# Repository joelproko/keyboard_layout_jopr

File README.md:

# keyboard_layout_jopr
This is my first attempt at a custom keyboard. It's inspired, among others, by https://github.com/itractus/KeyBored  
The firmware is located at https://github.com/joelproko/qmk_firmware/tree/jopr

This is a layout of what the microcontroller will probably send for which key:  

"default":  
  
[Keyboard Layout Editor link](http://www.keyboard-layout-editor.com/#/gists/82594aeadc8321c39f5dd5e3733b16e5)

"modded-white": (based on https://github.com/mw8/white_keyboard_layout)  
  
[Keyboard Layout Editor link](http://www.keyboard-layout-editor.com/#/gists/e355f587c1d4540c1ec2808fc14671c6)

This a keycap design for the latter:  
  
[Keyboard Layout Editor link](http://www.keyboard-layout-editor.com/#/gists/73444aee1e5caa922be72c5b2b2db0ba)

There's a PDF of the schematic

and a PDF of the PCB
 (and [a version with separate pages for each layer](https://github.com/joelproko/keyboard_layout_jopr/raw/master/keyboard_layout_jopr.kicad_pcb.page_per_layer.pdf))

2019-06-22:  
So far, the PCB and the keycaps have arrived. I made a low quality photo on my phone.

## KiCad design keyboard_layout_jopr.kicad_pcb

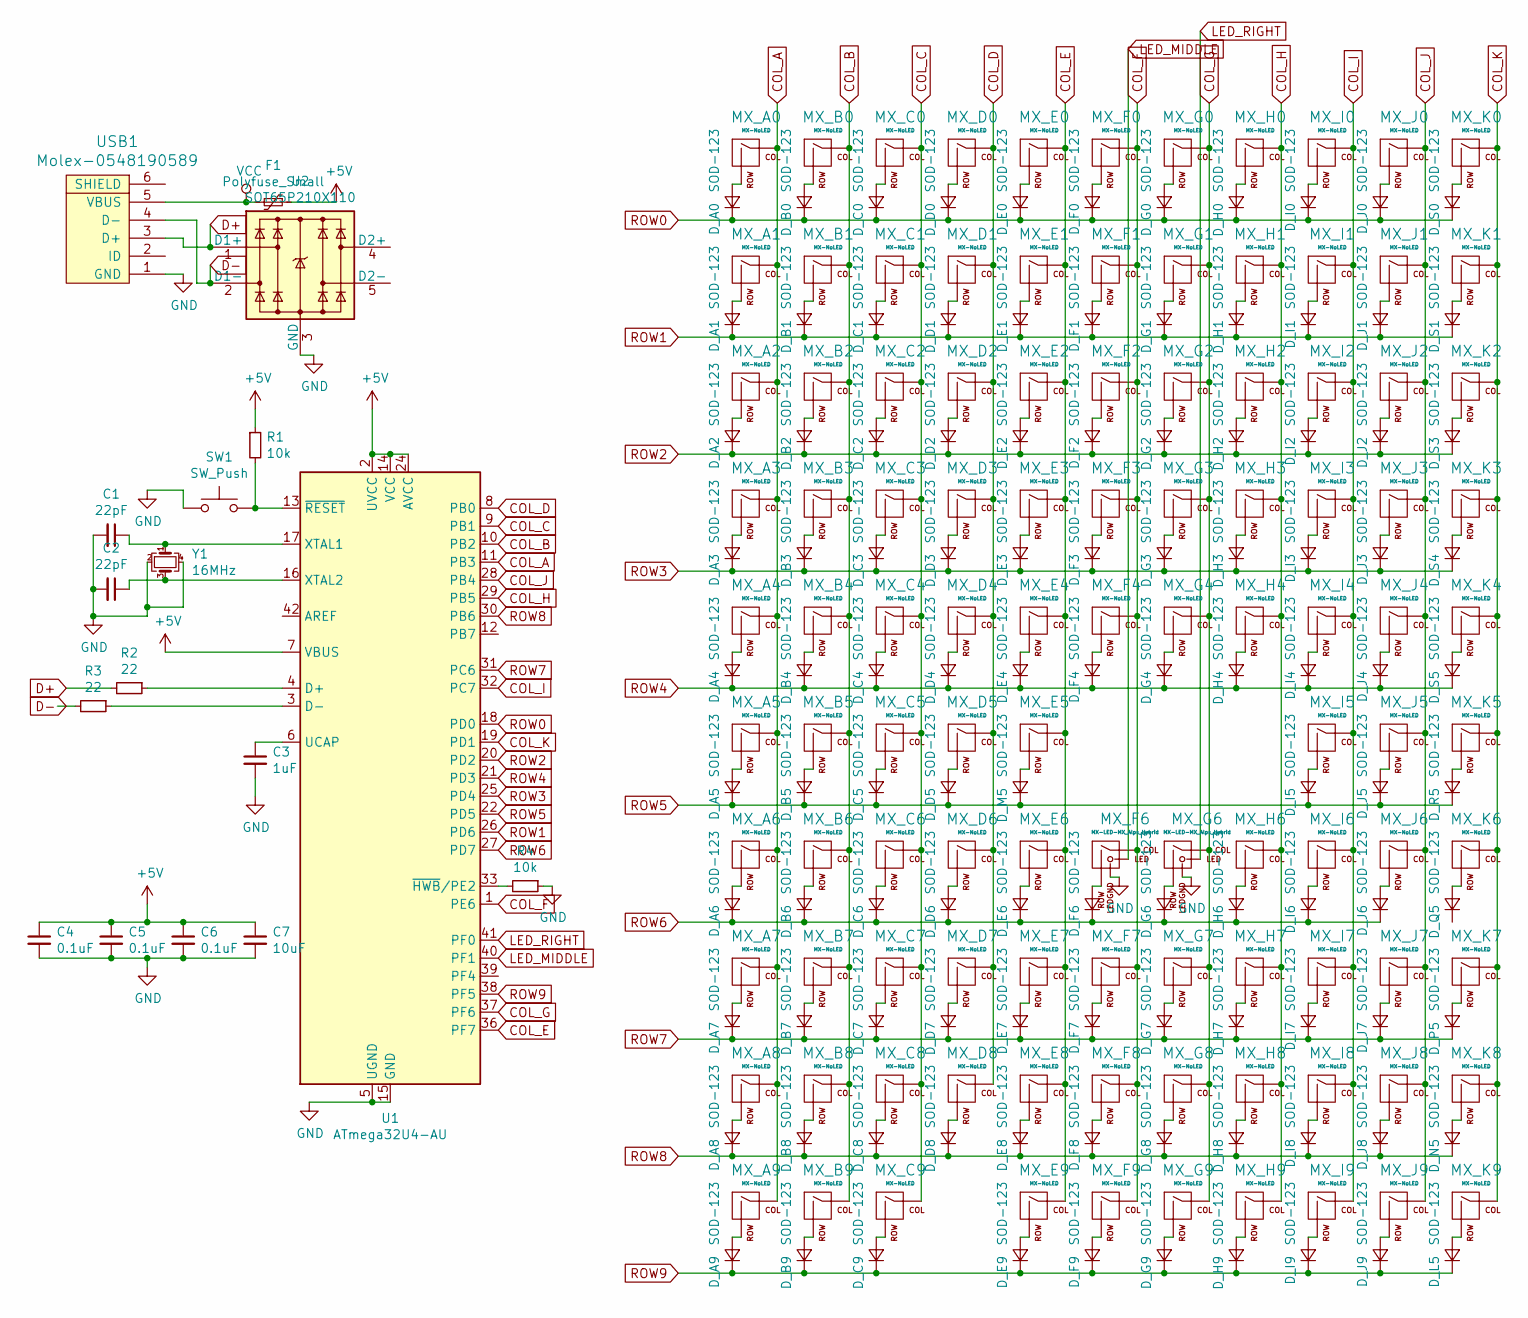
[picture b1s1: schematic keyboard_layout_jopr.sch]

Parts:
C1, C2: 22pF; C_0805_2012Metric
C3: 1uF; C_0805_2012Metric
C4, C5, C6: 0.1uF; C_0805_2012Metric
C7: 10uF; C_0805_2012Metric
D_A0, D_A1, D_A2, D_A3, D_A4, D_A5, D_A6, D_A7, D_A8, D_A9: SOD-123; D_SOD-123
D_B0, D_B1, D_B2, D_B3, D_B4, D_B5, D_B6, D_B7, D_B8, D_B9: SOD-123; D_SOD-123
D_C0, D_C1, D_C2, D_C3, D_C4, D_C5, D_C6, D_C7, D_C8, D_C9: SOD-123; D_SOD-123
D_D0, D_D1, D_D2, D_D3, D_D4, D_D5, D_D6, D_D7, D_D8: SOD-123; D_SOD-123
D_E0, D_E1, D_E2, D_E3, D_E4, D_E6, D_E7, D_E8, D_E9: SOD-123; D_SOD-123
D_F0, D_F1, D_F2, D_F3, D_F4, D_F6, D_F7, D_F8, D_F9: SOD-123; D_SOD-123
D_G0, D_G1, D_G2, D_G3, D_G4, D_G6, D_G7, D_G8, D_G9: SOD-123; D_SOD-123
D_H0, D_H1, D_H2, D_H3, D_H4, D_H6, D_H7, D_H8, D_H9: SOD-123; D_SOD-123
D_I0, D_I1, D_I2, D_I3, D_I4, D_I5, D_I6, D_I7, D_I8, D_I9: SOD-123; D_SOD-123
D_J0, D_J1, D_J2, D_J3, D_J4, D_J5, D_J6, D_J7, D_J8, D_J9: SOD-123; D_SOD-123
D_L5: SOD-123; D_SOD-123
D_M5: SOD-123; D_SOD-123
D_N5: SOD-123; D_SOD-123
D_P5: SOD-123; D_SOD-123
D_Q5: SOD-123; D_SOD-123
D_R5: SOD-123; D_SOD-123
D_S0, D_S1, D_S3, D_S4, D_S5: SOD-123; D_SOD-123
F1: Polyfuse_Small; Fuse_1206_3216Metric
MX_A0, MX_A1, MX_A6, MX_A7, MX_A8, MX_A9: MX-NoLED; MXOnly-1U-NoLED
MX_A2: MX-NoLED; MXOnly-1.5U-NoLED
MX_A3: MX-NoLED; MXOnly-1.75U-NoLED
MX_A4, MX_A5: MX-NoLED; MXOnly-1.25U-NoLED
MX_B0, MX_B1, MX_B2, MX_B3, MX_B4, MX_B6, MX_B7, MX_B8, MX_B9: MX-NoLED; MXOnly-1U-NoLED
MX_B5: MX-NoLED; MXOnly-1.25U-NoLED
MX_C0, MX_C1, MX_C2, MX_C3, MX_C4, MX_C6, MX_C7, MX_C8, MX_C9: MX-NoLED; MXOnly-1U-NoLED
MX_C5: MX-NoLED; MXOnly-1.25U-NoLED
MX_D0, MX_D1, MX_D2, MX_D3, MX_D4, MX_D6: MX-NoLED; MXOnly-1U-NoLED
MX_D5: MX-NoLED; MXOnly-6.25U-NoLED
MX_D7: MX-NoLED; MXOnly-2U-NoLED
MX_D8: MX-NoLED; MXOnly-ISO-NoLED
MX_E0, MX_E1, MX_E2, MX_E3, MX_E4, MX_E6, MX_E7, MX_E8, MX_E9: MX-NoLED; MXOnly-1U-NoLED
MX_E5: MX-NoLED; MXOnly-1.25U-NoLED
MX_F0, MX_F1, MX_F2, MX_F3, MX_F4, MX_F7, MX_F8, MX_F9: MX-NoLED; MXOnly-1U-NoLED
MX_F6: MX-LED-MX_Alps_Hybrid; MXOnly-1U-FLIPPED
MX_G0, MX_G1, MX_G2, MX_G3, MX_G4, MX_G7, MX_G8, MX_G9: MX-NoLED; MXOnly-1U-NoLED
MX_G6: MX-LED-MX_Alps_Hybrid; MXOnly-1U-FLIPPED
MX_H0, MX_H1, MX_H2, MX_H3, MX_H4, MX_H6, MX_H7, MX_H9: MX-NoLED; MXOnly-1U-NoLED
MX_H8: MX-NoLED; MXOnly-2U-NoLED
MX_I0, MX_I1, MX_I2, MX_I3, MX_I4, MX_I6, MX_I8, MX_I9: MX-NoLED; MXOnly-1U-NoLED
MX_I5: MX-NoLED; MXOnly-1.25U-NoLED
MX_I7: MX-NoLED; MXOnly-2.75U-NoLED
MX_J0, MX_J1, MX_J2, MX_J3, MX_J4, MX_J6, MX_J8, MX_J9: MX-NoLED; MXOnly-1U-NoLED
MX_J5: MX-NoLED; MXOnly-1.25U-NoLED
MX_J7: MX-NoLED; MXOnly-2U-NoLED
MX_K0, MX_K1, MX_K2, MX_K3, MX_K4, MX_K5, MX_K6, MX_K7: MX-NoLED; MXOnly-1U-NoLED
MX_K8: MX-NoLED; MXOnly-2U-NoLED
MX_K9: MX-NoLED; MXOnly-1.25U-NoLED
R1, R4: 10k; R_0805_2012Metric
R2, R3: 22; R_0805_2012Metric
SW1: SW_Push; SKQG-1155865
U1: ATmega32U4-AU; TQFP-44_10x10mm_P0.8mm
U2: SOT65P210X110; SOT65P210X110-6N
USB1: Molex-0548190589
Y1: 16MHz; Crystal_SMD_3225-4Pin_3.2x2.5mm

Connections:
+5V: C4.1, C5.1, C6.1, C7.1, F1.1, R1.1, U1.2 (UVCC), U1.7 (VBUS), U1.14 (VCC), U1.24 (AVCC), U1.34 (VCC), U1.44 (AVCC)
COL_A: MX_A0.1 (COL), MX_A1.1 (COL), MX_A2.1 (COL), MX_A3.1 (COL), MX_A4.1 (COL), MX_A5.1 (COL), MX_A6.1 (COL), MX_A7.1 (COL), MX_A8.1 (COL), MX_A9.1 (COL), U1.11 (PB3)
COL_B: MX_B0.1 (COL), MX_B1.1 (COL), MX_B2.1 (COL), MX_B3.1 (COL), MX_B4.1 (COL), MX_B5.1 (COL), MX_B6.1 (COL), MX_B7.1 (COL), MX_B8.1 (COL), MX_B9.1 (COL), U1.10 (PB2)
COL_C: MX_C0.1 (COL), MX_C1.1 (COL), MX_C2.1 (COL), MX_C3.1 (COL), MX_C4.1 (COL), MX_C5.1 (COL), MX_C6.1 (COL), MX_C7.1 (COL), MX_C8.1 (COL), MX_C9.1 (COL), U1.9 (PB1)
COL_D: MX_D0.1 (COL), MX_D1.1 (COL), MX_D2.1 (COL), MX_D3.1 (COL), MX_D4.1 (COL), MX_D5.1 (COL), MX_D6.1 (COL), MX_D7.1 (COL), MX_D8.1 (COL), U1.8 (PB0)
COL_E: MX_E0.1 (COL), MX_E1.1 (COL), MX_E2.1 (COL), MX_E3.1 (COL), MX_E4.1 (COL), MX_E5.1 (COL), MX_E6.1 (COL), MX_E7.1 (COL), MX_E8.1 (COL), MX_E9.1 (COL), U1.36 (PF7)
COL_F: MX_F0.1 (COL), MX_F1.1 (COL), MX_F2.1 (COL), MX_F3.1 (COL), MX_F4.1 (COL), MX_F6.1 (COL), MX_F7.1 (COL), MX_F8.1 (COL), MX_F9.1 (COL), U1.1 (PE6)
COL_G: MX_G0.1 (COL), MX_G1.1 (COL), MX_G2.1 (COL), MX_G3.1 (COL), MX_G4.1 (COL), MX_G6.1 (COL), MX_G7.1 (COL), MX_G8.1 (COL), MX_G9.1 (COL), U1.37 (PF6)
COL_H: MX_H0.1 (COL), MX_H1.1 (COL), MX_H2.1 (COL), MX_H3.1 (COL), MX_H4.1 (COL), MX_H6.1 (COL), MX_H7.1 (COL), MX_H8.1 (COL), MX_H9.1 (COL), U1.29 (PB5)
COL_I: MX_I0.1 (COL), MX_I1.1 (COL), MX_I2.1 (COL), MX_I3.1 (COL), MX_I4.1 (COL), MX_I5.1 (COL), MX_I6.1 (COL), MX_I7.1 (COL), MX_I8.1 (COL), MX_I9.1 (COL), U1.32 (PC7)
COL_J: MX_J0.1 (COL), MX_J1.1 (COL), MX_J2.1 (COL), MX_J3.1 (COL), MX_J4.1 (COL), MX_J5.1 (COL), MX_J6.1 (COL), MX_J7.1 (COL), MX_J8.1 (COL), MX_J9.1 (COL), U1.28 (PB4)
COL_K: MX_K0.1 (COL), MX_K1.1 (COL), MX_K2.1 (COL), MX_K3.1 (COL), MX_K4.1 (COL), MX_K5.1 (COL), MX_K6.1 (COL), MX_K7.1 (COL), MX_K8.1 (COL), MX_K9.1 (COL), U1.19 (PD1)
D+: R2.2, U2.1 (D1+), USB1.3 (D+)
D-: R3.2, U2.2 (D1-), USB1.4 (D-)
GND: C1.2, C2.2, C3.2, C4.2, C5.2, C6.2, C7.2, MX_F6.4 (LEDGND), MX_G6.4 (LEDGND), R4.1, SW1.1, U1.5 (UGND), U1.15 (GND), U1.23 (GND), U1.35 (GND), U1.43 (GND), U2.3 (GND), U2.8 (GND), USB1.1 (GND), Y1.2, Y1.4
LED_MIDDLE: MX_F6.3 (LED), U1.40 (PF1)
LED_RIGHT: MX_G6.3 (LED), U1.41 (PF0)
unnamed: C1.1, U1.17 (XTAL1), Y1.1
unnamed: C2.1, U1.16 (XTAL2), Y1.3
unnamed: C3.1, U1.6 (UCAP)
unnamed: D_A0.2 (A), MX_A0.2 (ROW)
unnamed: D_A1.2 (A), MX_A1.2 (ROW)
unnamed: D_A2.2 (A), MX_A2.2 (ROW)
unnamed: D_A3.2 (A), MX_A3.2 (ROW)
unnamed: D_A4.2 (A), MX_A4.2 (ROW)
unnamed: D_A5.2 (A), MX_A5.2 (ROW)
unnamed: D_A6.2 (A), MX_A6.2 (ROW)
unnamed: D_A7.2 (A), MX_A7.2 (ROW)
unnamed: D_A8.2 (A), MX_A8.2 (ROW)
unnamed: D_A9.2 (A), MX_A9.2 (ROW)
unnamed: D_B0.2 (A), MX_B0.2 (ROW)
unnamed: D_B1.2 (A), MX_B1.2 (ROW)
unnamed: D_B2.2 (A), MX_B2.2 (ROW)
unnamed: D_B3.2 (A), MX_B3.2 (ROW)
unnamed: D_B4.2 (A), MX_B4.2 (ROW)
unnamed: D_B5.2 (A), MX_B5.2 (ROW)
unnamed: D_B6.2 (A), MX_B6.2 (ROW)
unnamed: D_B7.2 (A), MX_B7.2 (ROW)
unnamed: D_B8.2 (A), MX_B8.2 (ROW)
unnamed: D_B9.2 (A), MX_B9.2 (ROW)
unnamed: D_C0.2 (A), MX_C0.2 (ROW)
unnamed: D_C1.2 (A), MX_C1.2 (ROW)
unnamed: D_C2.2 (A), MX_C2.2 (ROW)
unnamed: D_C3.2 (A), MX_C3.2 (ROW)
unnamed: D_C4.2 (A), MX_C4.2 (ROW)
unnamed: D_C5.2 (A), MX_C5.2 (ROW)
unnamed: D_C6.2 (A), MX_C6.2 (ROW)
unnamed: D_C7.2 (A), MX_C7.2 (ROW)
unnamed: D_C8.2 (A), MX_C8.2 (ROW)
unnamed: D_C9.2 (A), MX_C9.2 (ROW)
unnamed: D_D0.2 (A), MX_D0.2 (ROW)
unnamed: D_D1.2 (A), MX_D1.2 (ROW)
unnamed: D_D2.2 (A), MX_D2.2 (ROW)
unnamed: D_D3.2 (A), MX_D3.2 (ROW)
unnamed: D_D4.2 (A), MX_D4.2 (ROW)
unnamed: D_D5.2 (A), MX_D5.2 (ROW)
unnamed: D_D6.2 (A), MX_D6.2 (ROW)
unnamed: D_D7.2 (A), MX_D7.2 (ROW)
unnamed: D_D8.2 (A), MX_D8.2 (ROW)
unnamed: D_E0.2 (A), MX_E0.2 (ROW)
unnamed: D_E1.2 (A), MX_E1.2 (ROW)
unnamed: D_E2.2 (A), MX_E2.2 (ROW)
unnamed: D_E3.2 (A), MX_E3.2 (ROW)
unnamed: D_E4.2 (A), MX_E4.2 (ROW)
unnamed: D_E6.2 (A), MX_E6.2 (ROW)
unnamed: D_E7.2 (A), MX_E7.2 (ROW)
unnamed: D_E8.2 (A), MX_E8.2 (ROW)
unnamed: D_E9.2 (A), MX_E9.2 (ROW)
unnamed: D_F0.2 (A), MX_F0.2 (ROW)
unnamed: D_F1.2 (A), MX_F1.2 (ROW)
unnamed: D_F2.2 (A), MX_F2.2 (ROW)
unnamed: D_F3.2 (A), MX_F3.2 (ROW)
unnamed: D_F4.2 (A), MX_F4.2 (ROW)
unnamed: D_F6.2 (A), MX_F6.2 (ROW)
unnamed: D_F7.2 (A), MX_F7.2 (ROW)
unnamed: D_F8.2 (A), MX_F8.2 (ROW)
unnamed: D_F9.2 (A), MX_F9.2 (ROW)
unnamed: D_G0.2 (A), MX_G0.2 (ROW)
unnamed: D_G1.2 (A), MX_G1.2 (ROW)
unnamed: D_G2.2 (A), MX_G2.2 (ROW)
unnamed: D_G3.2 (A), MX_G3.2 (ROW)
unnamed: D_G4.2 (A), MX_G4.2 (ROW)
unnamed: D_G6.2 (A), MX_G6.2 (ROW)
unnamed: D_G7.2 (A), MX_G7.2 (ROW)
unnamed: D_G8.2 (A), MX_G8.2 (ROW)
unnamed: D_G9.2 (A), MX_G9.2 (ROW)
unnamed: D_H0.2 (A), MX_H0.2 (ROW)
unnamed: D_H1.2 (A), MX_H1.2 (ROW)
unnamed: D_H2.2 (A), MX_H2.2 (ROW)
unnamed: D_H3.2 (A), MX_H3.2 (ROW)
unnamed: D_H4.2 (A), MX_H4.2 (ROW)
unnamed: D_H6.2 (A), MX_H6.2 (ROW)
unnamed: D_H7.2 (A), MX_H7.2 (ROW)
unnamed: D_H8.2 (A), MX_H8.2 (ROW)
unnamed: D_H9.2 (A), MX_H9.2 (ROW)
unnamed: D_I0.2 (A), MX_I0.2 (ROW)
unnamed: D_I1.2 (A), MX_I1.2 (ROW)
unnamed: D_I2.2 (A), MX_I2.2 (ROW)
unnamed: D_I3.2 (A), MX_I3.2 (ROW)
unnamed: D_I4.2 (A), MX_I4.2 (ROW)
unnamed: D_I5.2 (A), MX_I5.2 (ROW)
unnamed: D_I6.2 (A), MX_I6.2 (ROW)
unnamed: D_I7.2 (A), MX_I7.2 (ROW)
unnamed: D_I8.2 (A), MX_I8.2 (ROW)
unnamed: D_I9.2 (A), MX_I9.2 (ROW)
unnamed: D_J0.2 (A), MX_J0.2 (ROW)
unnamed: D_J1.2 (A), MX_J1.2 (ROW)
unnamed: D_J2.2 (A), MX_J2.2 (ROW)
unnamed: D_J3.2 (A), MX_J3.2 (ROW)
unnamed: D_J4.2 (A), MX_J4.2 (ROW)
unnamed: D_J5.2 (A), MX_J5.2 (ROW)
unnamed: D_J6.2 (A), MX_J6.2 (ROW)
unnamed: D_J7.2 (A), MX_J7.2 (ROW)
unnamed: D_J8.2 (A), MX_J8.2 (ROW)
unnamed: D_J9.2 (A), MX_J9.2 (ROW)
unnamed: D_L5.2 (A), MX_K9.2 (ROW)
unnamed: D_M5.2 (A), MX_E5.2 (ROW)
unnamed: D_N5.2 (A), MX_K8.2 (ROW)
unnamed: D_P5.2 (A), MX_K7.2 (ROW)
unnamed: D_Q5.2 (A), MX_K6.2 (ROW)
unnamed: D_R5.2 (A), MX_K5.2 (ROW)
unnamed: D_S0.2 (A), MX_K0.2 (ROW)
unnamed: D_S1.2 (A), MX_K1.2 (ROW)
unnamed: D_S3.2 (A), MX_K2.2 (ROW)
unnamed: D_S4.2 (A), MX_K3.2 (ROW)
unnamed: D_S5.2 (A), MX_K4.2 (ROW)
unnamed: R1.2, SW1.2, U1.13 (~RESET)
unnamed: R2.1, U1.4 (D+)
unnamed: R3.1, U1.3 (D-)
unnamed: R4.2, U1.33 (~HWB~/PE2)
ROW0: D_A0.1 (K), D_B0.1 (K), D_C0.1 (K), D_D0.1 (K), D_E0.1 (K), D_F0.1 (K), D_G0.1 (K), D_H0.1 (K), D_I0.1 (K), D_J0.1 (K), D_S0.1 (K), U1.18 (PD0)
ROW1: D_A1.1 (K), D_B1.1 (K), D_C1.1 (K), D_D1.1 (K), D_E1.1 (K), D_F1.1 (K), D_G1.1 (K), D_H1.1 (K), D_I1.1 (K), D_J1.1 (K), D_S1.1 (K), U1.26 (PD6)
ROW2: D_A2.1 (K), D_B2.1 (K), D_C2.1 (K), D_D2.1 (K), D_E2.1 (K), D_F2.1 (K), D_G2.1 (K), D_H2.1 (K), D_I2.1 (K), D_J2.1 (K), D_S3.1 (K), U1.20 (PD2)
ROW3: D_A3.1 (K), D_B3.1 (K), D_C3.1 (K), D_D3.1 (K), D_E3.1 (K), D_F3.1 (K), D_G3.1 (K), D_H3.1 (K), D_I3.1 (K), D_J3.1 (K), D_S4.1 (K), U1.25 (PD4)
ROW4: D_A4.1 (K), D_B4.1 (K), D_C4.1 (K), D_D4.1 (K), D_E4.1 (K), D_F4.1 (K), D_G4.1 (K), D_H4.1 (K), D_I4.1 (K), D_J4.1 (K), D_S5.1 (K), U1.21 (PD3)
ROW5: D_A5.1 (K), D_B5.1 (K), D_C5.1 (K), D_D5.1 (K), D_I5.1 (K), D_J5.1 (K), D_M5.1 (K), D_R5.1 (K), U1.22 (PD5)
ROW6: D_A6.1 (K), D_B6.1 (K), D_C6.1 (K), D_D6.1 (K), D_E6.1 (K), D_F6.1 (K), D_G6.1 (K), D_H6.1 (K), D_I6.1 (K), D_J6.1 (K), U1.27 (PD7)
ROW7: D_A7.1 (K), D_B7.1 (K), D_C7.1 (K), D_D7.1 (K), D_E7.1 (K), D_F7.1 (K), D_G7.1 (K), D_H7.1 (K), D_I7.1 (K), D_J7.1 (K), D_P5.1 (K), U1.31 (PC6)
ROW8: D_A8.1 (K), D_B8.1 (K), D_C8.1 (K), D_D8.1 (K), D_E8.1 (K), D_F8.1 (K), D_G8.1 (K), D_H8.1 (K), D_I8.1 (K), D_J8.1 (K), D_N5.1 (K), U1.30 (PB6)
ROW9: D_A9.1 (K), D_B9.1 (K), D_C9.1 (K), D_E9.1 (K), D_F9.1 (K), D_G9.1 (K), D_H9.1 (K), D_I9.1 (K), D_J9.1 (K), D_L5.1 (K), U1.38 (PF5)
VCC: F1.2, USB1.5 (VBUS)

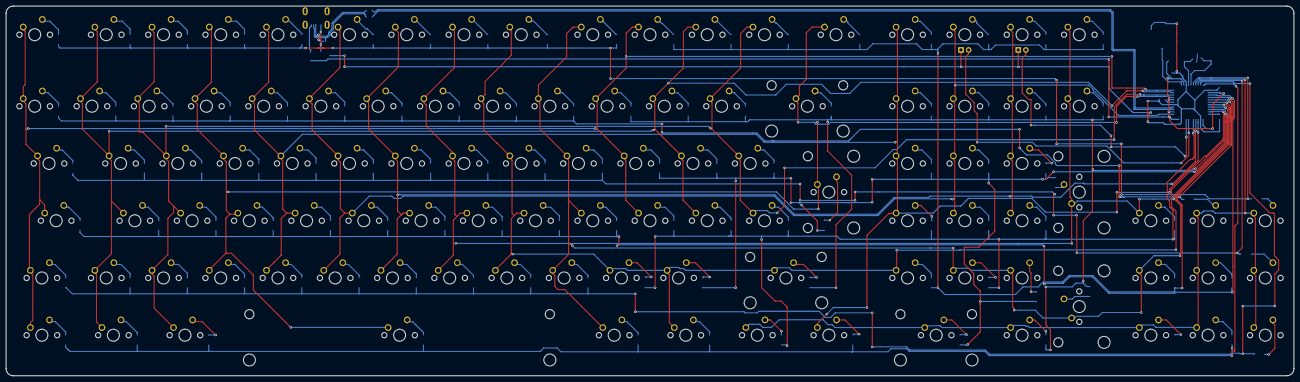
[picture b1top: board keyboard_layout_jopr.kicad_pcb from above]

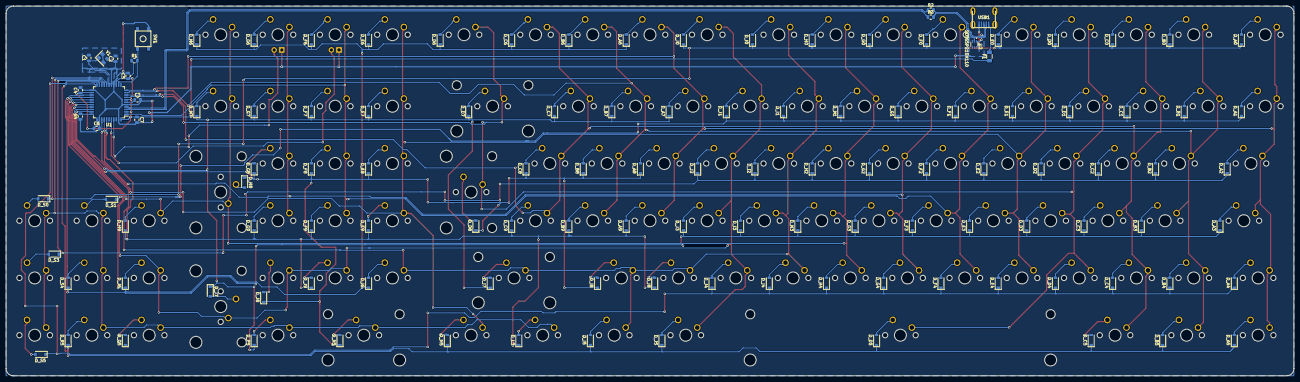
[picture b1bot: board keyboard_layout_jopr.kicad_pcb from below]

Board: 2 copper layers, 428.6 x 123.0 mm, 229 parts (123 on the bottom side), 141 nets.

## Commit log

2019-06-07 kicad init
2019-06-07 Add submodules
2019-06-07 added libraries
2019-06-08 maybe done with the kicad part?
2019-06-08 Inter-key tracks and USB Data tracks only
2019-06-08 maybe better tracks
2019-06-08 ran DRC
2019-06-09 replaced MX_Hybrid with MX_Only footprints
2019-06-09 PDF-Versions of current state of schematic and pcb
2019-06-09 added keycode layout preview
2019-06-10 added ESD-protection
2019-06-10 updated PDFs
2019-06-11 squared matrix, updated and renamed PDFs
2019-06-11 generated Gerber files
2019-06-11 moved lower edge down
2019-06-11 moved lower PCB edge down
2019-06-11 added LEDs for Lock keys
2019-06-11 removed NumLock
2019-06-11 updated Gerber Zip
2019-06-17 updated JSON and PNG files of keycode layouts
2019-06-17 Added keycap layout
